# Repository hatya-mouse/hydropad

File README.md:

# HydroPad

HydroPad is a macropad with some holes for the water to go through, designed for people with palmar hyperhidrosis.

## Gallery

*Screenshot of the assembled model*

*Schematic of HydroPad*

*PCB layout of HydroPad*

*Top plate design*

*Bottom case design*

## Required Components

- 1x PCB
- 1x Top Plate
- 1x Bottom Case

- 1x Seeed XIAO RP2040
- 6x through-hole 1N4148 Diodes
- 5x MX-Style switches
- 1x EC11 Rotary encoders
- 1x 0.91 inch OLED display
- 5x blank DSA keycaps
- 4x M3x5mx4mm heatset inserts
(I'll use my own screws instead of M3x16mm screws included in the kit)

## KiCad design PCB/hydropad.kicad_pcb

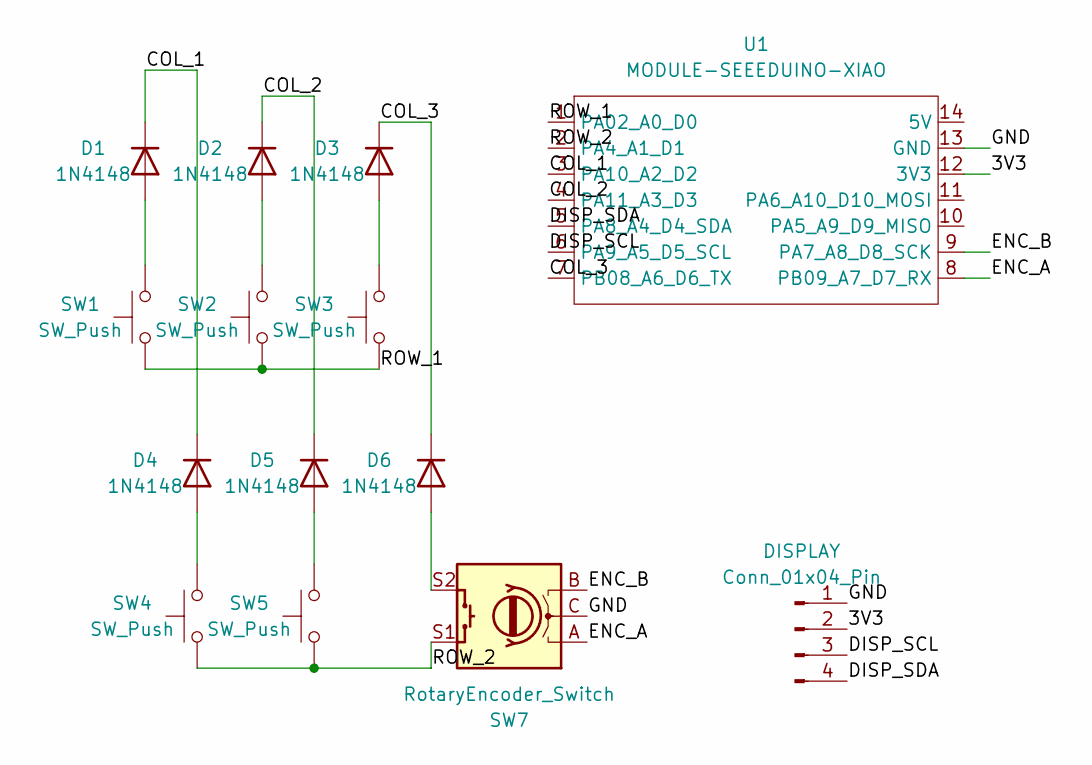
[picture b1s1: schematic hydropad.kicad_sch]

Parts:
D1, D2, D3, D4, D5, D6: 1N4148; D_DO-35_SOD27_P7.62mm_Horizontal
DISPLAY: Conn_01x04_Pin; PinHeader_1x04_P2.54mm_Vertical
SW1, SW2, SW3, SW4, SW5: SW_Push; SW_Cherry_MX_1.00u_PCB
SW7: RotaryEncoder_Switch; RotaryEncoder_Alps_EC11E-Switch_Vertical_H20mm
U1: MODULE-SEEEDUINO-XIAO; XIAO-Generic-Hybrid-14P-2.54-21X17.8MM

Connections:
/3V3: DISPLAY.2, U1.12 (3V3)
/COL_1: D1.1 (K), D4.1 (K), U1.3 (PA10_A2_D2)
/COL_2: D2.1 (K), D5.1 (K), U1.4 (PA11_A3_D3)
/COL_3: D3.1 (K), D6.1 (K), U1.7 (PB08_A6_D6_TX)
/DISP_SCL: DISPLAY.3, U1.6 (PA9_A5_D5_SCL)
/DISP_SDA: DISPLAY.4, U1.5 (PA8_A4_D4_SDA)
/ENC_A: SW7.A, U1.8 (PB09_A7_D7_RX); also elsewhere on the board
/ENC_B: SW7.B, U1.9 (PA7_A8_D8_SCK); also elsewhere on the board
/GND: DISPLAY.1, SW7.C, U1.13 (GND); also elsewhere on the board
/ROW_1: SW1.1, SW2.1, SW3.1, U1.1 (PA02_A0_D0)
/ROW_2: SW4.1, SW5.1, SW7.S1, U1.2 (PA4_A1_D1); also elsewhere on the board
unnamed: D1.2 (A), SW1.2
unnamed: D2.2 (A), SW2.2
unnamed: D3.2 (A), SW3.2
unnamed: D4.2 (A), SW4.2
unnamed: D5.2 (A), SW5.2
unnamed 16: D6.2 (A), SW7.S2; also elsewhere on the board

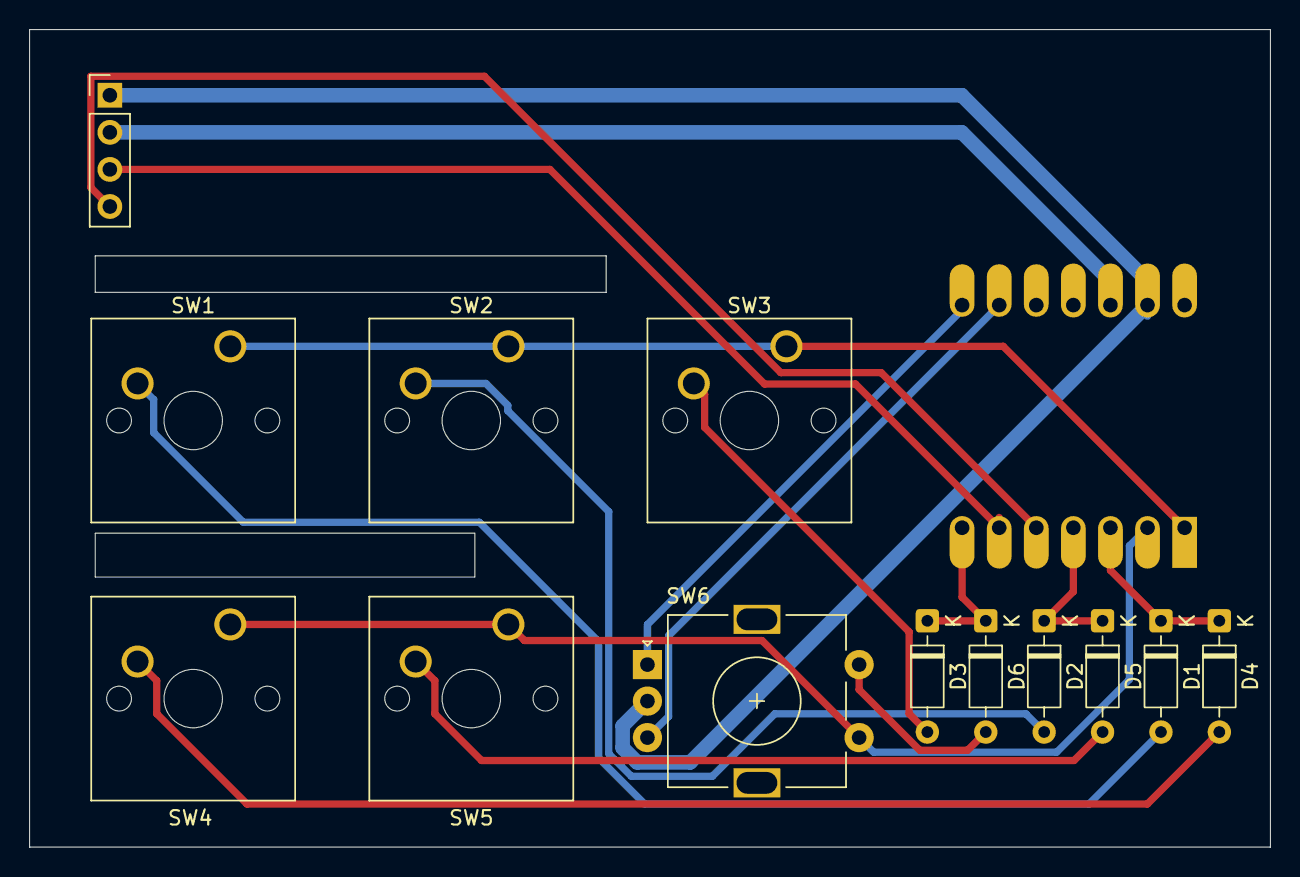
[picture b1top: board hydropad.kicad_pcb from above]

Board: 2 copper layers, 85.0 x 56.0 mm, 14 parts (1 on the bottom side), 17 nets.

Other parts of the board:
SW6: RotaryEncoder_Switch; RotaryEncoder_Alps_EC11E-Switch_Vertical_H20mm

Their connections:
/ENC_A: SW6.A; also elsewhere on the board
/ENC_B: SW6.B; also elsewhere on the board
/GND: SW6.C; also elsewhere on the board
/ROW_2: SW6.S1; also elsewhere on the board
unnamed 16: SW6.S2; also elsewhere on the board

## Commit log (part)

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2026-06-04 chore: initial commit
2026-06-04 chore: add PCB/.history to gitignore
2026-06-04 feat: add firmware and set up keyboard.json
2026-06-04 feat: add some features to keyboard.json
2026-06-04 feat: add simple encoder and oled implementation
2026-06-04 chore: add PCB/~hydropad* to gitignore
2026-06-04 fix: reapply .gitignore rules
2026-06-04 feat: render qmk logo
2026-06-04 Add some CAD data
2026-06-04 docs: add some images to README
2026-06-04 fix: fix firmware syntax and compile the binary
2026-06-04 docs: update image of assembled model in README.md
2026-06-04 docs: fix image urls
2026-06-04 docs: update the description
2026-06-04 fix: rename step files to meet the requirements
2026-06-07 docs: fix introduction text
2026-06-07 docs: fix the name of the disease
2026-06-07 Create CNAME
